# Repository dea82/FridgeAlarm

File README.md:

# FridgeAlarm

## System overview
Alarm system for unintentionally open fridge door

## Requirements

## Design
### Component selection

### Box design

### PCB

### Software
[Doxygen documentation](http://dea82.github.io/FridgeAlarm)

#### Doxygen deployment by Travis
The source code documentation is generated with [Doxygen](http://www.doxygen.com) and pushed automatically to GitHub Pages by [Travis CI](http://www.travis-ci.org).

##### Setup
This assumes that you've already figures out how to genereate Doxygen documentation and are able to build with Travis CI.

To be able to automatically update Doxygen documentation when a commit is done to GitHub follow these steps:
###### Generation of SSH-key
1. Generate a new SSH key with the following command: 
`ssh-keygen -t rsa -b 4096 -C "your_email@example.com"`
2. You are then prompted to enter a name for the new keypair. Enter a file in which to save the key.
3. When asked for passphrase just press ENTER for empty passphrase. Confirm with ENTER again.

###### Setup GitHub
1. Navigate to your GitHub settings page `https://github.com/<username>/<your_repository>/settings/keys` and paste the content from the public ssh-key file, the one ending with .pub. **Make sure to check the box that allows write access!**

###### Setup Travis CI
This is the trickiest part.
1. Make sure you're able to connect to Travis console.
2. Run command: `travis encrypt-file name-of-key-generated`.
It's the key that doesn't end with .pub that shall be used.
3. You get an instruction from Travis CI. As it says you should now make sure to add the returned key, ending with .enc, to your repository. All others keys can and should now be removed!
4. Next update your .travis.yml with the encryption label, the 12-digit hex value returned from step 2.
```
env:
	global:
    	- ENCRYPTION_LABEL: "12-digit hex value"
```
TODO: Finalize
https://gist.github.com/domenic/ec8b0fc8ab45f39403dd

## Verification

### Install
To upload the hex-file to the MCU (Attiny85) I use the following command with avrdude:
`avrdude -B250 -cusbasp -pt85 -Uflash:w:<path to hex file> -Ulfuse:w:0xE2:m -Uhfuse:w:0x55:m`
The -B250 makes it slow - however if the clock of the MCU is to slow it might not work otherwise.

#### Fuses
|MCU      |Low fuse|High fuse|
|---------|:------:|:-------:|
|Attiny13A|0x7A    |0xFA     |
|Attiny85 |0xE2    |0x55     |
### Power consumption
The following current consumption has been observed: 
#### Development PCB (Attiny85 with magnetic buzzer)
|System mode      |Current consumption [mA]|
|-----------------|:----------------------:|
|Buzzer and LED ON|42                      |
|LED ON           |2.3                     |
|Deep sleep       |0.024                   |
#### Production PCB (Attiny13A with piezo buzzer)
|System mode      |Current consumption mA  |
|-----------------|:----------------------:|
|Buzzer and LED ON|5                       |
|LED ON	          |2.2                     |
|Deep sleep	  |0.024                   |

## Conclusion

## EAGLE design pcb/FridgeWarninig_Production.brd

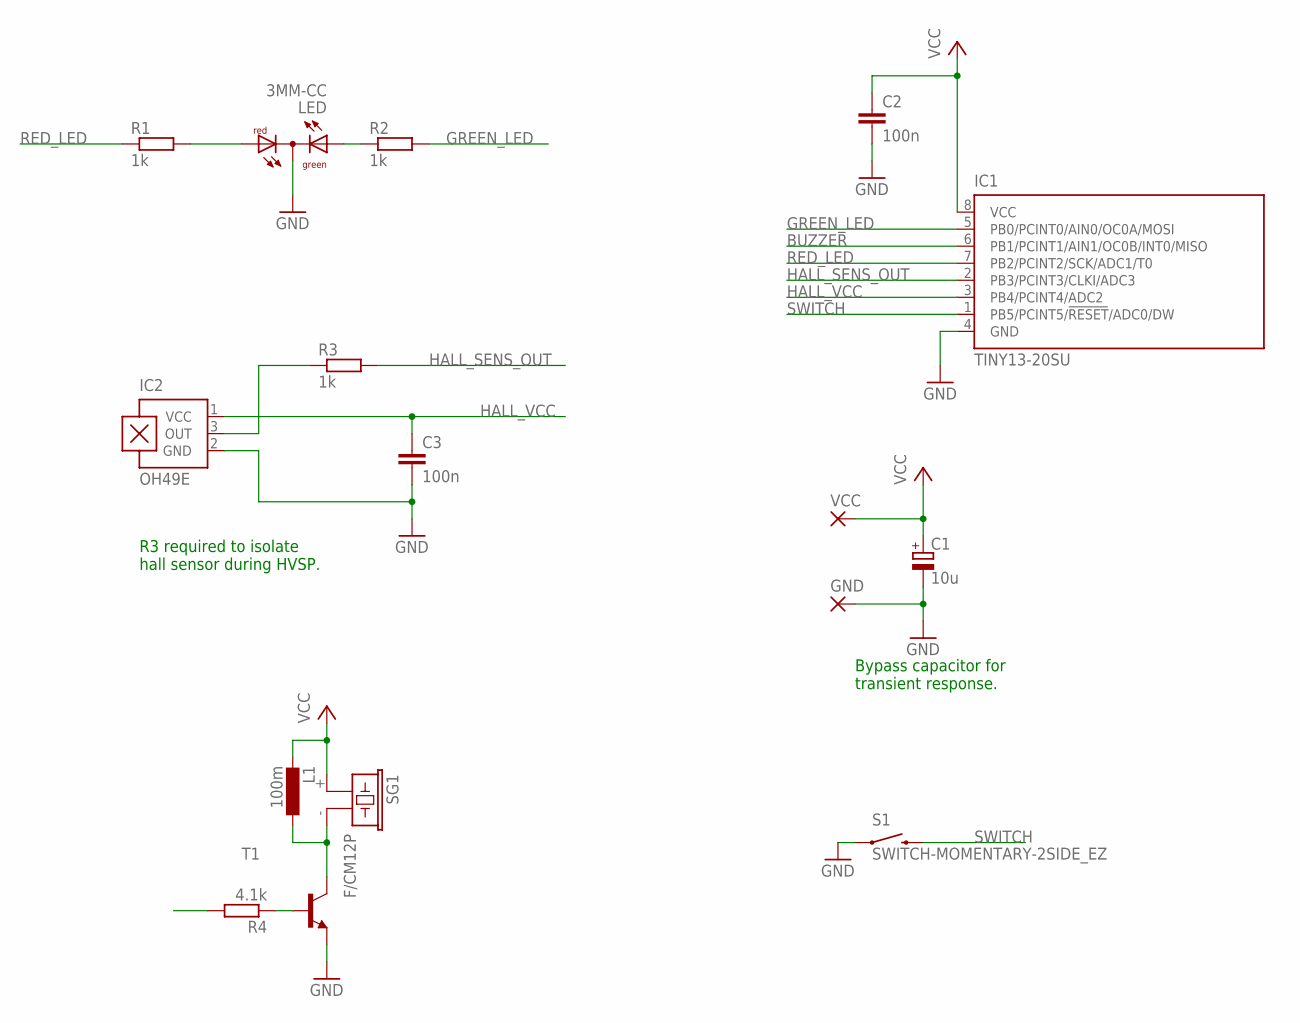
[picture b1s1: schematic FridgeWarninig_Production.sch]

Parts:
C1: 10u; 153CLV-0405
C2, C3: 100n; C0603
GND: 2,54/1,0
IC1: TINY13-20SU; 8S2
IC2: OH49E; SIP3-UA
L1: 100m; TT5D9L
LED: 3MM-CC; DUOLED-A-3MM
R1, R2, R3: 1k; R0603
R4: 4.1k; R0603
S1: SWITCH-MOMENTARY-2SIDE_EZ; TACTILE-PTH-SIDEEZ
SG1: F/CM12P
T1: MMBT918LT1-NPN-SOT23-BEC; SOT23-BEC
VCC: 2,54/1,0

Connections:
BUZZER: IC1.6 (PB1/PCINT1/AIN1/OC0B/INT0/MISO), R4.2
GND: C1.-, C2.2, C3.2, GND.1, IC1.4 (GND), IC2.2 (GND), LED.2 (C), S1.1, T1.E
GREEN_LED: IC1.5 (PB0/PCINT0/AIN0/OC0A/MOSI), R2.2
HALL_SENS_OUT: IC1.2 (PB3/PCINT3/CLKI/ADC3), R3.2
HALL_VCC: C3.1, IC1.3 (PB4/PCINT4/ADC2), IC2.1 (VCC)
unnamed: R4.1, T1.B
unnamed: L1.+ (1), SG1.- (2), T1.C
unnamed: IC2.3 (OUT), R3.1
unnamed: LED.1 (AG), R2.1
unnamed: LED.3 (AR), R1.2
RED_LED: IC1.7 (PB2/PCINT2/SCK/ADC1/T0), R1.1
SWITCH: IC1.1 (PB5/PCINT5/!RESET!/ADC0/DW), S1.2
VCC: C1.+, C2.1, IC1.8 (VCC), L1.- (2), SG1.+ (1), VCC.1

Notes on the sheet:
R3 required to isolate hall sensor during HVSP.
Bypass capacitor for transient response.

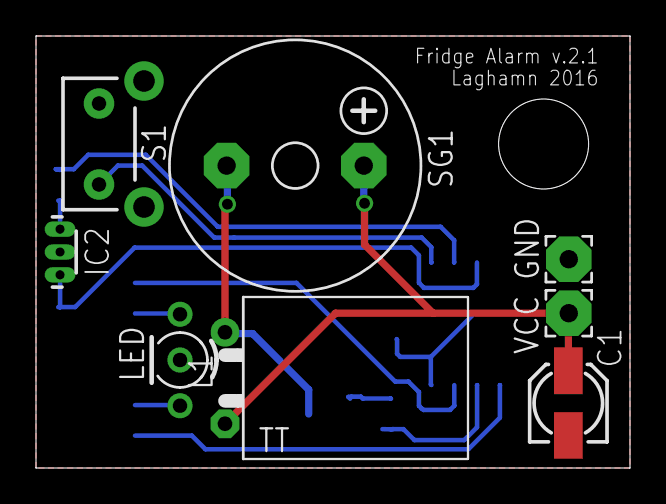
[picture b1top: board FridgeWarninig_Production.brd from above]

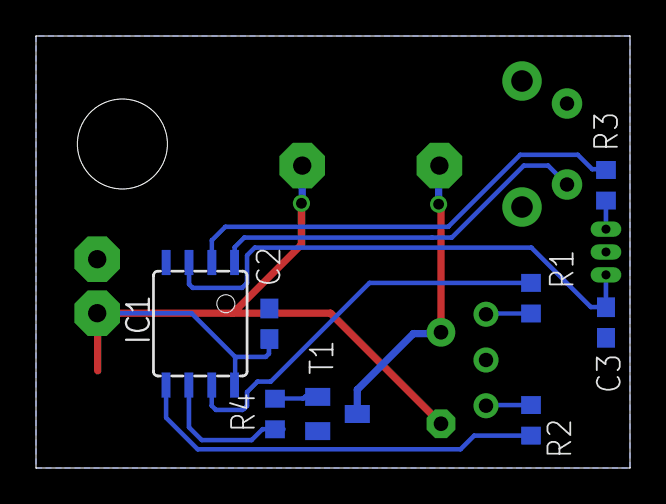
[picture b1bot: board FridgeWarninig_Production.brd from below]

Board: 2 copper layers, 33.0 x 24.0 mm, 16 parts (8 on the bottom side), 13 nets.

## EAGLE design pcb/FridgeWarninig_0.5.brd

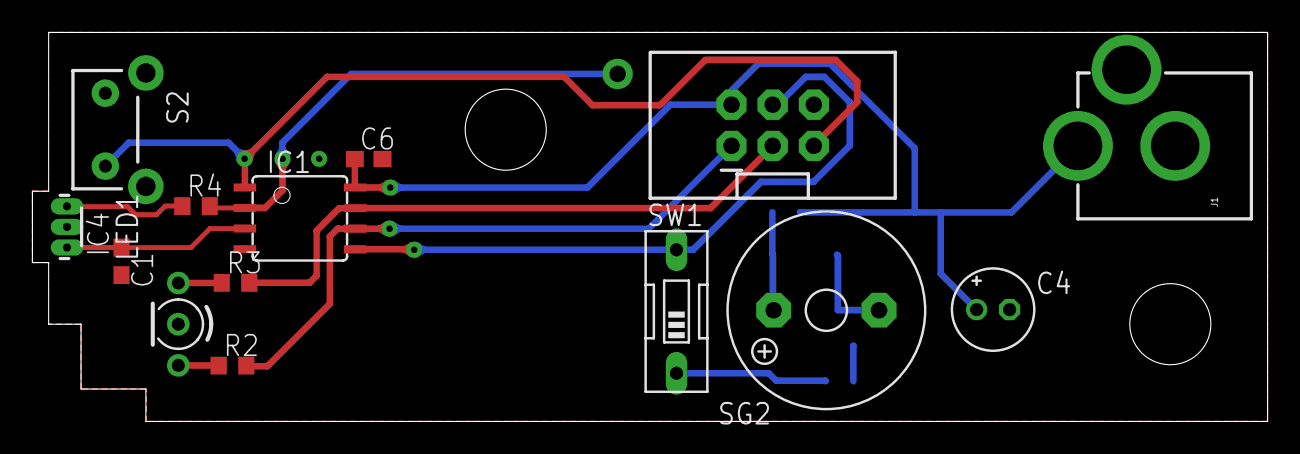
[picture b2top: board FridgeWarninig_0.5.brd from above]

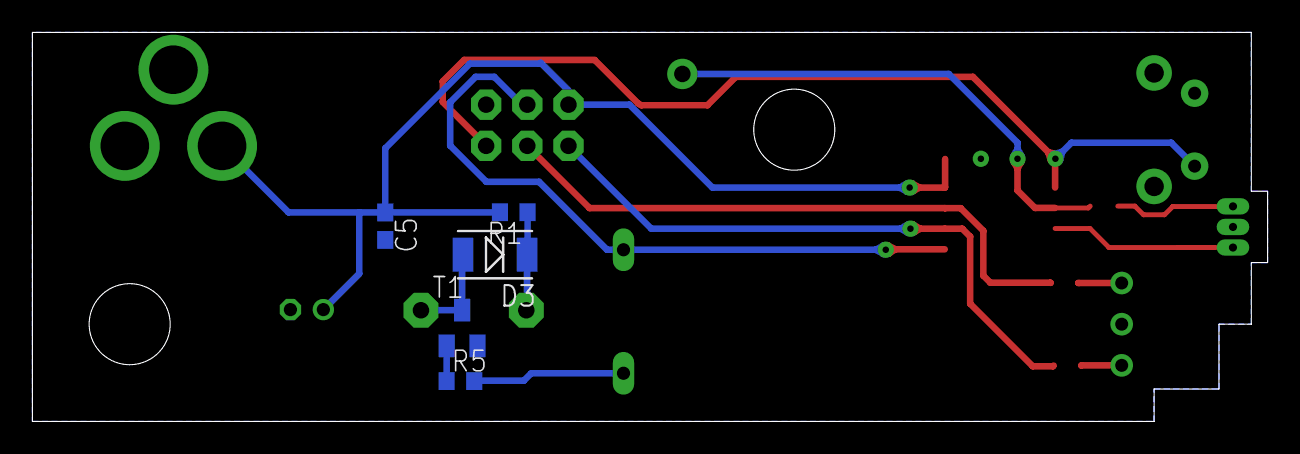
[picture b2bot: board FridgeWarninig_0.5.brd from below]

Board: 2 copper layers, 76.2 x 24.0 mm, 20 parts (5 on the bottom side), 15 nets.

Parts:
C1, C5, C6: 100n; C0603
C4: 10uF; E2-5
D3: DO-214AC
IC1: TINY13-20SU; 8S2
IC4: A1302UA; SIP3-UA
J1: POWER_JACKPTH; POWER_JACK_PTH
JP1: 2X3-SHROUDED
JP2: M01NOSILK-KIT; 1X01NS-KIT
LED1: L-115WEGW-CA; DUOLED-A-3MM
R1: 200; R0603
R2, R3: 150; R0603
R4: 1k; R0603
R5: 2k; R0603
S2: SWITCH-MOMENTARY-2SIDE_EZ; TACTILE-PTH-SIDEEZ
SG2: F/TMB
SW1: EDG-01
T1: BC847; SOT23

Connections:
GND: C1.2, C4.-, C5.2, C6.2, IC1.4, IC4.2, J1.GND, J1.GNDBREAK, JP1.6, LED1.2, S2.1, T1.2
GREEN_LED: LED1.1, R2.1
HALL_SENSOR: IC4.3, R4.1
HALL_SWITCH: C1.1, IC1.3, IC4.1
MISO: IC1.6, JP1.1, R2.2
MOSI: IC1.5, JP1.4, SW1.2
unnamed: R5.2, SW1.1
unnamed: D3.2, SG2.-, T1.3
unnamed: IC1.2, JP2.1, R4.2
unnamed: D3.1, R1.1, SG2.+
unnamed: R5.1, T1.1
RED_LED: LED1.3, R3.1
RESET: IC1.1, JP1.5, S2.2
SCK: IC1.7, JP1.3, R3.2
VCC: C4.+, C5.1, C6.1, IC1.8, J1.PWR, JP1.2, R1.2

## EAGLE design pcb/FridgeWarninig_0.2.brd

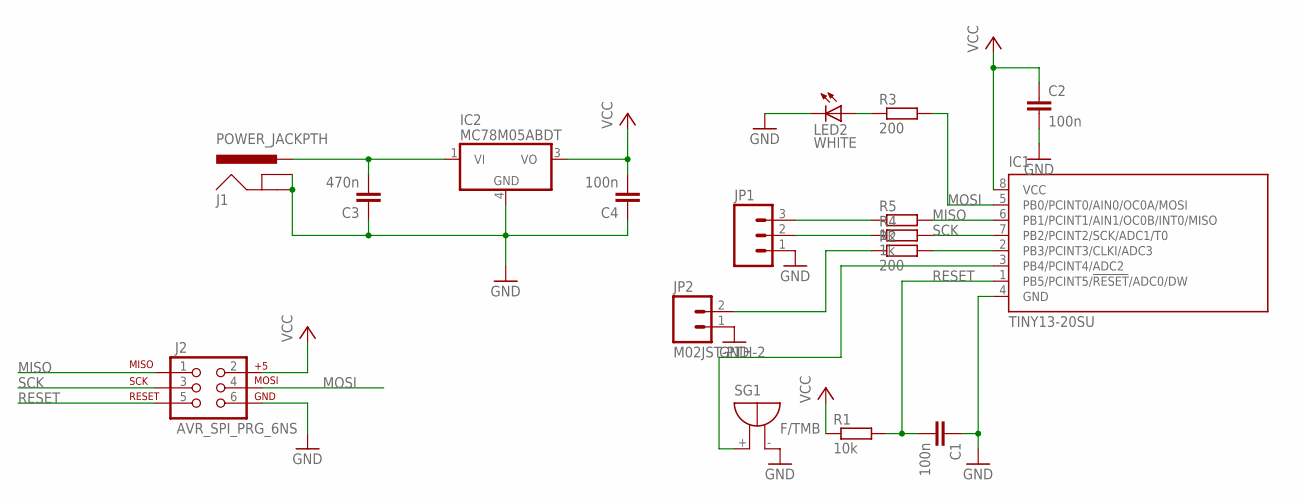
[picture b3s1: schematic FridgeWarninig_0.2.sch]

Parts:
C1, C2, C4: 100n; C0805
C3: 470n; C0805
IC1: TINY13-20SU; 8S2
IC2: MC78M05ABDT; DPACK_3
J1: POWER_JACKPTH; POWER_JACK_PTH
J2: AVR_SPI_PRG_6NS; 2X3-NS
JP1: M03JST-PTH; JST-3-PTH
JP2: M02JST-PTH-2; JST-2-PTH
LED2: WHITE; CHIP-LED0603
R1: 10k; R0805
R2: 200; R0805
R3: 200; R0603
R4, R5: 1k; R0805
SG1: F/TMB

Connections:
GND: C1.1, C2.2, C3.1, C4.1, IC1.4 (GND), IC2.4 (GND), J1.GND, J1.GNDBREAK, J2.6, JP1.1, JP2.1, LED2.C, SG1.-
MISO: IC1.6 (PB1/PCINT1/AIN1/OC0B/INT0/MISO), J2.1, R5.2
MOSI: IC1.5 (PB0/PCINT0/AIN0/OC0A/MOSI), J2.4, R3.2
unnamed: JP2.2, R2.1
unnamed: C3.2, IC2.1 (VI), J1.PWR
unnamed: IC1.3 (PB4/PCINT4/ADC2), SG1.+
unnamed: IC1.2 (PB3/PCINT3/CLKI/ADC3), R2.2
unnamed: JP1.2, R4.1
unnamed: LED2.A, R3.1
unnamed: JP1.3, R5.1
RESET: C1.2, IC1.1 (PB5/PCINT5/!RESET!/ADC0/DW), J2.5, R1.2
SCK: IC1.7 (PB2/PCINT2/SCK/ADC1/T0), J2.3, R4.2
VCC: C2.1, C4.2, IC1.8 (VCC), IC2.3 (VO), J2.2, R1.1

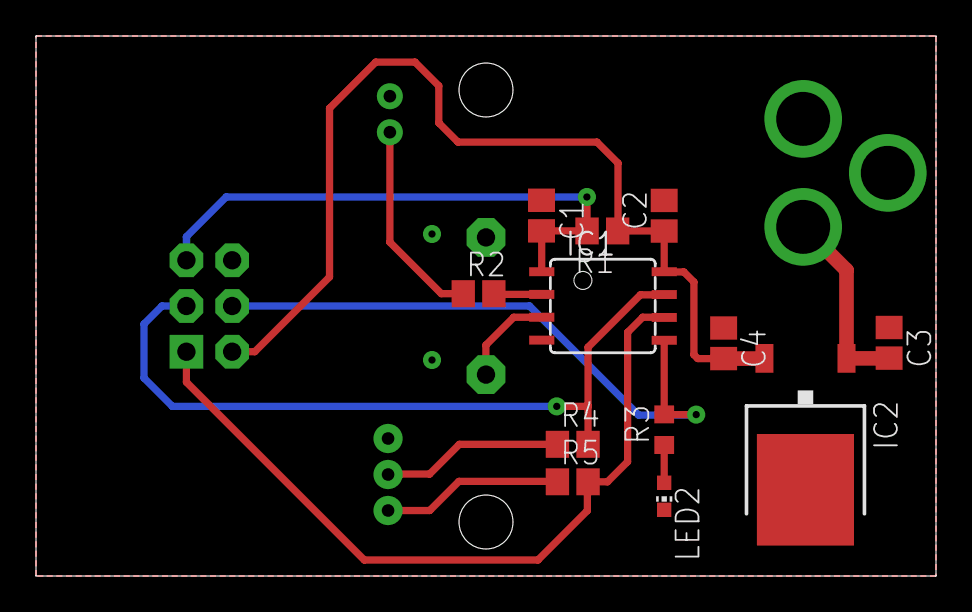
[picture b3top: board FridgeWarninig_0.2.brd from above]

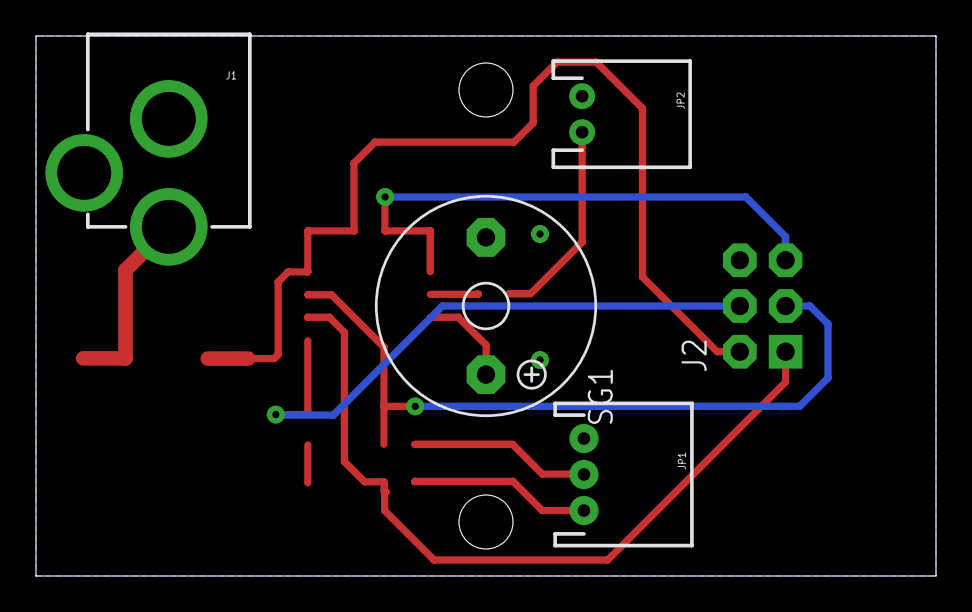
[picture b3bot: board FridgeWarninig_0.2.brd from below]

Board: 2 copper layers, 50.0 x 30.0 mm, 17 parts (5 on the bottom side), 13 nets.

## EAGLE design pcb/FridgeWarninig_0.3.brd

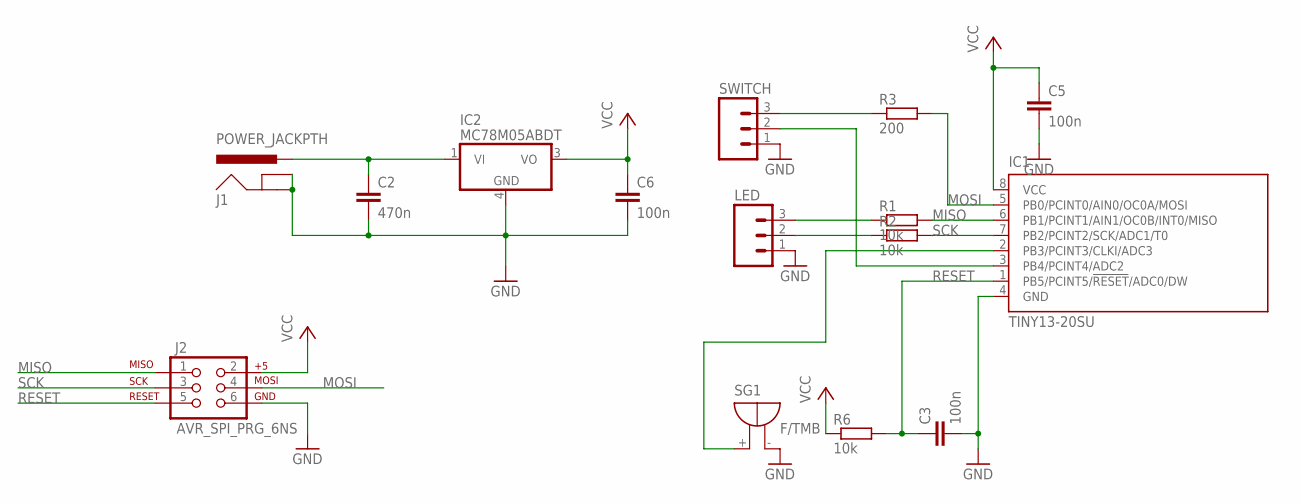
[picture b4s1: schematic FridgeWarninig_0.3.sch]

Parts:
C2: 470n; C0603
C3, C5, C6: 100n; C0603
IC1: TINY13-20SU; 8S2
IC2: MC78M05ABDT; DPACK_3
J1: POWER_JACKPTH; POWER_JACK_PTH
J2: AVR_SPI_PRG_6NS; 2X3-NS
LED: M03JST-PTH; JST-3-PTH
R1, R2, R6: 10k; R0603
R3: 200; R0603
SG1: F/TMB
SWITCH: M03JST-PTH; JST-3-PTH

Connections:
GND: C2.2, C3.2, C5.2, C6.2, IC1.4 (GND), IC2.4 (GND), J1.GND, J1.GNDBREAK, J2.6, LED.1, SG1.-, SWITCH.1
MISO: IC1.6 (PB1/PCINT1/AIN1/OC0B/INT0/MISO), J2.1, R1.2
MOSI: IC1.5 (PB0/PCINT0/AIN0/OC0A/MOSI), J2.4, R3.2
unnamed: C2.1, IC2.1 (VI), J1.PWR
unnamed: IC1.2 (PB3/PCINT3/CLKI/ADC3), SG1.+
unnamed: LED.2, R2.1
unnamed: R3.1, SWITCH.3
unnamed: LED.3, R1.1
unnamed: IC1.3 (PB4/PCINT4/ADC2), SWITCH.2
RESET: C3.1, IC1.1 (PB5/PCINT5/!RESET!/ADC0/DW), J2.5, R6.2
SCK: IC1.7 (PB2/PCINT2/SCK/ADC1/T0), J2.3, R2.2
VCC: C5.1, C6.1, IC1.8 (VCC), IC2.3 (VO), J2.2, R6.1

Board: 2 copper layers, 15 parts (5 on the bottom side), 12 nets, no tracks yet.

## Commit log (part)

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2015-02-18 Eclipse src code project.
2015-02-18 Updates of project settings.
2015-02-19 Upload PCB:s. Closes #4.
2015-02-28 Added a lot of new preliminary code: - Buzzer control - Led control - Scheduler - Switch monitor - New version of PCB - Configuration file
2015-02-28 Update led control.
2015-04-25 Added cad files and a lot others. Update before formatting local disk.
2015-05-31 13: CPU load - implement
    Task-Url: http://github.com/dea82/FridgeAlarm/issues/issue/13
2015-05-31 9: Create macros for IO control
    Task-Url: http://github.com/dea82/FridgeAlarm/issues/issue/9
    Close #9.
2015-06-01 Moved button interrupt en/disable to butt.
2015-06-01 Missed a lot of new files.
2015-06-03 Prototype code, everything seems to work at the moment. The code shall be cleaned and this is a less function version for Attiny13A. Simplified calibration etc.
    Close #5
2015-06-09 Updated CAD-drawings. Only holes for speaker missing.
2015-06-09 Added holes for speaker.
2015-06-10 Made a huge clean of unnecessary files.
2015-06-24 Optimized code. Final CAD-model of case.
2015-06-25 Revert "Added door state partially open which will enable a shorter alarm time for a door which seems closed but isn't."
    This reverts commit 34d5dfc61c6f11f07fcf84b0bc87ceb58ea36388.
2015-07-07 19: Watchdog interrupt can freeze MCU
    Task-Url: http://github.com/dea82/FridgeAlarm/issues/issue/19
2015-07-20 Added transistor to supply hall-sensor.
2015-07-21 23: Bug in butt module
    Task-Url: http://github.com/dea82/FridgeAlarm/issues/issue/23
2015-07-21 Inlined init and loop functions.
2015-10-26 Updates after converting to battery power supply.
2015-11-02 Commit before merging to master.
2015-11-02 26: Create uart-files
    Task-Url: http://github.com/dea82/FridgeAlarm/issues/issue/26
2015-11-05 #Close 29: Uart transmit
    Task-Url: http://github.com/dea82/FridgeAlarm/issues/issue/29
2015-11-09 Started to work on part module.
2015-11-09 Change output filename.
2015-11-11 Puts output files into a separate directory.
2015-11-11 Ignoring output folder.
2015-11-19 Updated Makefile to output into a separate directory.
2015-12-02 Update uart_asm.S
    Removed unnecessary set carry instruction
    It's not necessary to set the carry flag due to the fact that instuction, com, does that already. Saves 2 bytes.
2015-12-02 Clean up some unused defines
    Unused defines for TX/RX status have been removed.
2015-12-08 Define macros used for timing delay in uart
    Added a couple of timing delays used by uart.
2015-12-08 Cleanup of macros in uart.
    Balanced macros and also created a function that balances the extra delays needed.
2015-12-08 Cleanup of art.
2015-12-08 General uart update.
2015-12-08 36: Move baudrate to configuration file
    Task-Url: http://github.com/dea82/FridgeAlarm/issues/issue/36
    Close #36.
2015-12-09 General cleanup of uart
    Cleanup of uart assembler file.
2015-12-10 Use relaxation of linker
2015-12-11 39: Enable disable uart function
    Task-Url: http://github.com/dea82/FridgeAlarm/issues/issue/39
    Closes #39.
2015-12-14 Possibility to measure cycles.
2015-12-17 Enable BOD and disable it during sleep.
2015-12-18 Removed unnecessary BOD disable code
    There were some unnecessary (not working) code for BOD disable during sleep. This has now been removed.
2015-12-23 Various small fixes.
2015-12-25 Fix #48: Disable Timer0
    Task-Url: http://github.com/dea82/FridgeAlarm/issues/issue/48
2015-12-26 Update ignore rules.
2015-12-28 Update ignore rule.
2016-01-05 Const declare argument.
2016-04-12 Add comment what the purpose is of cpul
2016-04-15 Move maxNumberCycles for cpu load to assembly file
    For better encapsulation the max number of cycles has been moved to assembly file.
2016-04-15 Clear overflow flag before starting timer
    The overflow flag was no cleared before starting the timer for cpu load calculation.
2016-04-17 Add user defined prescaler cpu load
    Added possibility to specify which prescaler that shall be used with the cpu load start function.
2016-04-19 Minor small fix using macro _BV instead of <<
2016-05-02 Use Link Time Optimization (LTO)
    Added LTO in Makefile. This will save som amount of bytes.
2016-05-09 Renamed files for pcb proto board
2016-05-10 Optimizations in makefile settings
    1. lto - (link time optimization), does not make unnecessary calls to functions in other files. See all files as one single file.
    2. gc-sections - does not link functions that are not called.
    3. nostartfiles - define the interrupt vector self. Does not need to initialize stack pointer etc. New file created boot.S which contains the reset/interrupt vector.
2016-05-10 Update avr-gcc on travis server
2016-05-10 Cleanup in .gitignore file
2016-05-10 Added ignores in .gitignore
2016-05-10 Add sw bod disable and renamed function
2016-05-11 Corrected bug in sleep
2016-05-11 Updated Makefile for more debug info in lss
2016-05-11 Corrected if directives to a mcu that was recognized
2016-05-13 Power consumption fixes and possibility to restart from BOD
2016-05-22 A lot of refactoring and restructure
2016-05-23 Const declare arguments
    Close #50
2016-05-24 Added support for 9600000 clock in buzzer. Buzz is not run when uart is enabled.
2016-05-24 Delete Eclipse files
    Close #61.
2016-05-24 Corrected an include in wdtc
2016-05-31 New makefile for multiple targets
2016-06-01 Make builds targets but must be cleaned between switching targets.
2016-06-15 Added support for generation dependency files for assembly files. Did som cleanup for FLAGS, removed ALL_CFLAGS and ALL_AFLAGS as these were not necessary any more.
2016-06-15 Generating list-file #60 Further cleanup of Makefile and now generating list-file.
2016-06-15 Makefile - New options added: Debug, cpu load, baud rate
    New possible flags added to Makefile, #60:
    DEBUG_ENABLE: Makes it possible to output something on uart.
    CPU_LOAD: Outputs the actual load of the cpu.
    BAUD_RATE: The actual uart baud rate.
2016-06-15 Don't build attiny13a with CPU_LOAD=1
    Attiny13a does not have a Timer1 which makes it impossible to build attiny13a with flag CPU_LOAD=1 as this uses Timer1.
2016-06-15 Update travis file to find out doxygen version on Travis
2016-06-15 Updated travis file to install Doxygen and Graphviz
2016-06-15 Get rid of warnings for doxygen genereration
2016-06-15 Updated travis file to run publish script
2016-06-15 Update Travis files with ssh-keys to be able to push from travis
2016-06-16 Updated Doxygen comment to verify deployment
2016-06-16 Verifying that nothing will be deployed
2016-06-16 Verify that updated comments get deployed
2016-06-16 Reorganize deployment scripts to .deployment directory
2016-06-16 Travis: Deploy to GitHub Pages 113309f223e2ede5f45498ac8f8b926ee6d0bae6
2016-06-16 Comment about deployment in README.md
2016-06-16 Bug fixes after testing on HW
    Several bugs were detected:
    - WDT must be reset immediatly after wakeup. If button interrupt puts the MCU out of sleep, the WDT could have any value and WDT reset can happen at any time.
    - Function in wctc to enable/disable interrupt was not working correctly.
    - Seems that MCU hangs if global interrupt is not enabled before going to ADC Noise reduction mode.
    Implemented compensation for supply loss to hall sensor compared to ADC supply. Fixes #62.
    Still some things to investigate. Reset causes etc.
2016-06-16 Investigation of #57 and #58
    Global interrupt is not enabled automatically bu enabling WDT! Global interrupt must be manually enabled with sei(). Fix #58.
    The clearing of WDT seems to work. Fix #57. However the archtecture for indicating abnormal reset is not good enough. It shold be made as a separate branch not going through all loops again. For exam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
2016-06-16 Updated README with avrdude information and fuses
2016-06-16 Added a link to Doxygen documentation in README
2016-06-16 Added several .c files for doxygen generation
2016-06-16 Trying to create headers for assebly files
    This will make it possible to create Doxygen comments for assembly functions.
2016-06-16 Removed todo comment
2016-06-16 Travis: Deploy to GitHub Pages 71b71b8d47e6ff6cdb08129c9fecce1099effa02
2016-06-17 Replaced old error indicator function
    Replaced the old code for putting the MCU to deep sleep with orange led. Now it's not dependent of the normal function loop which could cause it to hang again when an AD conversion takes to long time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
2016-06-20 Travis: Deploy to GitHub Pages 3a3836a436807a27b9ffbcbccbb6e630538d93a4
2016-06-29 First run with uncrustify on src code.
2016-06-29 Travis: Deploy to GitHub Pages 3dc152c918de3e35f295ab73ed0423567ba4e7e7
2016-07-07 Travis: Deploy to GitHub Pages 67ffc83bdc46706a4111a20f7ff4b1c304538c2c
2016-07-07 Travis: Deploy to GitHub Pages c7050e72d711278558b85b3df86ea34065a588ae
2016-07-14 Travis: Deploy to GitHub Pages 6960a7251ce864f0c38f927c3cf3f3bcf724adf8
2016-08-19 Travis: Deploy to GitHub Pages d7badec2a153de25c79e6c91af407022eb8ad954
2016-08-19 Added warning for unused macros
    Closes #69
2016-08-19 Travis: Deploy to GitHub Pages d2c766a646d03707d6fa2756ce2bbe35a7a52ab7
2016-08-25 Updated piezo-test file
2016-08-30 Code style updates cleanup of schematic
2016-08-30 Travis: Deploy to GitHub Pages 224c61034a19a68eababf80a9ade287e43158c33
2016-09-14 Travis: Deploy to GitHub Pages 68e337ba6708ccdc370e9198d4dad57573f3dc5b
2016-09-19 Implement own version of crc8
    Travis has a pretty old avr-libc without support for CRC8. Instead fighting with updates of Travis now cpul includes it's own CRC8 calculation.
2016-09-20 Remove macro for adding tasks and replace with function
    Have replaced the macros used for dispatching the tasks and replaced with one function containing #if calls depending if CPU_LOAD is enabled or not. Have made some adjustment of Makefile and enabled 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
2016-09-26 Add licens file to satisfy Coverity Scan
2016-09-27 Restructure cpu load and rename to mcul
2016-09-28 Rename mcul to wcet
2016-09-28 Refactoring macros, inlining and optimization
    Fixes #76.
    Fixes #75.
    Fixes #73.
2016-09-30 Rename addTask function to dispatchTask
2016-09-30 Corrected PWM mode for piezo tester program.
2016-09-30 Move files from scripts to more general tools
2016-10-01 Fix typo in interrupt table
    Due to a typo in interrupt table Attiny13A did not get a correct interrupt table.
2016-10-01 Update preprocessor clauses
    Inhibit build for other than Attiny13A and Attiny85. Updated Travis file to support WCET variable.
2016-10-01 Calibrate buzzer
    Buzzer has been calibrated to 600 Hz and 10% duty cycle.
2016-10-01 Travis: Deploy to GitHub Pages 36c75a0263f8abdef214936cddc71a2b42efc2de
2016-10-01 Travis: Deploy to GitHub Pages 1c3a9936e6626b8a5862b7bdc31e88907ebb9174
2016-10-01 Add latest version of PCB drawing
2016-10-20 Change parameters to const
2016-11-10 Replace defines with const variables
    Replace defines with const variables for better debugging possibilities
    and type checkning.
    Replace ABS macro with stdlib abs().
2016-11-10 Fix overflow of buzzer freq calculation
    When changing to const variables instead of defines an overlow
    occured of U16 type when build fot attiny85. Added a U32 type to
    take care of that problem.
2016-11-11 Fix crc checksum calculation
    CRC checksum member in result block was not initialized which caused faulty CRC.
2017-01-05 Add CMakeBuild environment
2017-01-12 First version that works and gives same binary size as previous build system
2017-01-18 Commit before formatting computer
2017-02-19 Adapt to new cmake build
2017-02-19 Add Dockerfile
2017-02-21 Remove cpu load monitoring script
    This was far from ready not even prototype status. Removed it as Qt application will replace it.
2017-02-25 Replace crc8 with lib function
2017-02-26 Travis: Deploy to GitHub Pages 77606b8185d0c510a3613b49dca6e0d5a81ee38b
2017-02-26 Add build directory to ignorefile
2017-02-26 Remove unused function in avr cmake toolchain
2017-02-26 Formatting and fatal error if avr-gcc not found
2017-03-02 Remove define variables
    Removed define variables and created a new module conf.c which contains all user calibration parameters.
2017-03-02 Place extern declaration in headerfile
    Move extern function declaration from c to header file.
2017-03-02 Removed unnecessary build define
2017-03-03 Travis: Deploy to GitHub Pages b582bc3bf0ac3d0e8ff609ef455ce46dd96bc059
2018-02-15 Rename pointer variable names

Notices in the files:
parts and their libraries:
SparkFun-Connectors: Licensing: Creative Commons ShareAlike 4.0 International - https://creativecommons.org/licenses/by-sa/4.0
